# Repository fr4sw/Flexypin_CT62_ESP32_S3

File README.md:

Plaquette développée sous Kicad 9

Destinée à permettre l'expérimentation des ESP32, ESP32-S3, ESP32-C3 et Helltec CT62 (ESP32-C3+SX1262 (Lora)

Le systeme Flexypin peut permettre une vérification et programmation (par exemple pour implémenter l'OTA) avant soudure

Sur le PCB les pins sont indiquées Wroom=ESP32 puis S3 puis CT62.

Pour le CT62, les 2 pins du haut sont inutilisées.

Liens : 

- https://heltec.org/project/ht-ct62/

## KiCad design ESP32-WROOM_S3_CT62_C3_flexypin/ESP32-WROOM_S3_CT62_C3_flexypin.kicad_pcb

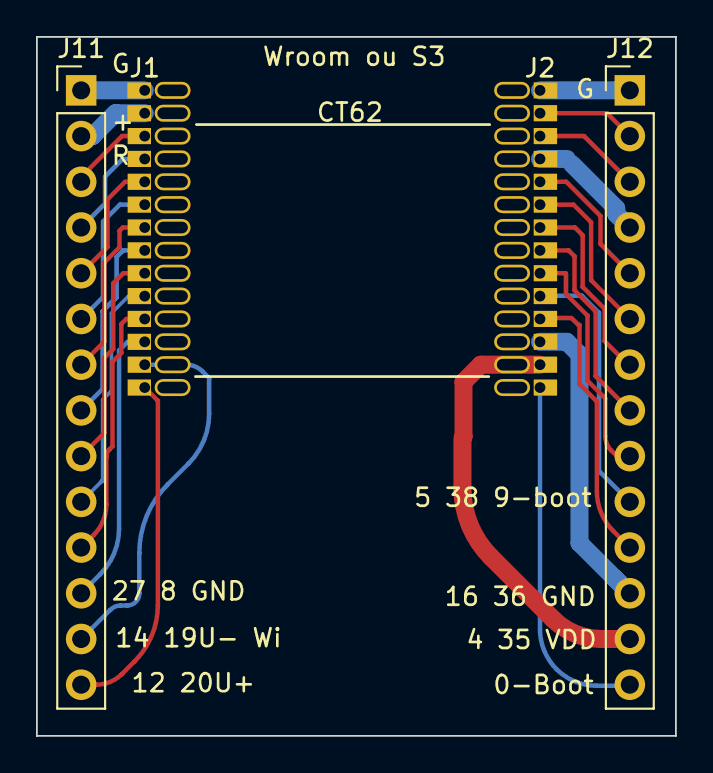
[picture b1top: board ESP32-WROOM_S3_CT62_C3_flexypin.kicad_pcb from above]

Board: 2 copper layers, 35.5 x 38.8 mm, 4 parts (0 on the bottom side), 28 nets.

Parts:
J1: Conn_01x14; FlexyPin_1x14_P1.27mm
J2: Conn_01x14; FlexyPin_1x14_P1.27mmMirror
J11, J12: Conn_01x14; PinHeader_1x14_P2.54mm_Vertical

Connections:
/0-Boot/W S3: J2.14, J12.14
/4/W 35/S3 VDD/62: J2.13, J12.13
/5/W 38/S3 9-boot/62: J2.10, J12.10
/12/W 20-U+/S3: J1.14, J11.14
/14/W 19-U-/S3 AntW/62: J1.13, J11.13
/16/W 36/S3 GND/62: J2.12, J12.12
/17/W 37/S3 10/62: J2.11, J12.11
/18/W 39/S3 8/62: J2.9, J12.9
/19/W 40/S3 18U-/62: J2.8, J12.8
/20/W 41/S3 19U+/62: J2.7, J12.7
/21/W 42/S3 RX/62: J2.6, J12.6
/22/W 2/S3 AntLora/62: J2.3, J12.3
/23/W 1/S3: J2.2, J12.2
/25/W 17/S3 6/62: J1.10, J11.10
/26/W 18/S3 7/62: J1.11, J11.11
/27/W 8/S3 GND/62: J1.12, J11.12
/32/W 15/S3 4/62: J1.8, J11.8
/33/W 16/S3 5/62: J1.9, J11.9
/34/W 6/S3 2/62: J1.6, J11.6
/35/W 7/S3 3/62: J1.7, J11.7
/EN-RST/W S3 62: J1.3, J11.3
/GND/W S3: J1.1, J11.1
/GND/W S3 (38): J2.1, J12.1
/RX/W S3 TX/62: J2.5, J12.5
/TX/W S3 GND/62: J2.4, J12.4
/VDD/W S3: J1.2, J11.2
/VN/W 5/S3 1/62: J1.5, J11.5
/VP/W 4/S3 0/62: J1.4, J11.4
